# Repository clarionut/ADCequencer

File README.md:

# ADCequencer
An 8 step dual channel sequencer with voltage controlled step pattern, based on the [Fonitronik VCPS8](http://www.modular.fonik.de/pdf/VCPS8_doc_v2.pdf) (the predecessor of the MH11) but with significant modifications.

Most obviously, there are two potentiometers to set CV voltages for each step and two CV output channels. This gives considerable flexibility - e.g. controlling two VCOs, a VCO and filter cutoff, or (in conjunction with an external clock divider / analogue switch module) operation as a 16-step sequencer.

Another significant visible change is the addition of a 'freeze' circuit operated by switch or a gate input allowing the ADC to be stopped under voltage control. This gives real value to the gate output from the VCPS8 (which is on continously through a sequence of active steps) as it allows the sequencer pattern to be updated only when the trigger output is low (generally meaning that no note is sounding). This avoids a serious glitchy effect when a step is turned off while it's active.

Cosmetically, the LED arrays have been replaced by red/white common-cathode bicolour LEDs associated with each step (red shows the active steps and white the current step) plus a red/blue common-anode LED as an indicator for out-of-range pattern control voltages.

Behind the scenes there are also significant changes:
- the PCV out-of-range protection circuit in the original is essentially a zener diode crowbar across an op-amp output. This has been replaced by an in-line resistor and Schottky diodes to +5V and ground. The PCV out is not clipped by these, so it's easy to use an external voltmeter to check and adjust the incoming control voltage. The out-of-range LED circuitry is also modified so the LEDs are never reverse biased.
- the Gray-coding circuitry is included but can be bypassed by connecting to an alternative header on the PCB. The CD4030 XOR gates can be omitted altogether if Gray-coding is not required.
- the gate/trigger driver circuit has been significantly revised, doing away with the need for the CD40106 in the original (discussion at [Electro-Music.com](https://electro-music.com/forum/topic-52774-50.html)). A simple RC filter on the base of the trigger-driver transistor removes the very fast pulse from the AND gates which can cause double-triggering. The CD40106 is not needed for the ADC clock either, as the ADC802 contains an inverter gate and just needs an external resistor and capacitor to provide its own clock. The gate and trigger outputs are taken from a dedicated 9V supply rather than the raw 12V supply.

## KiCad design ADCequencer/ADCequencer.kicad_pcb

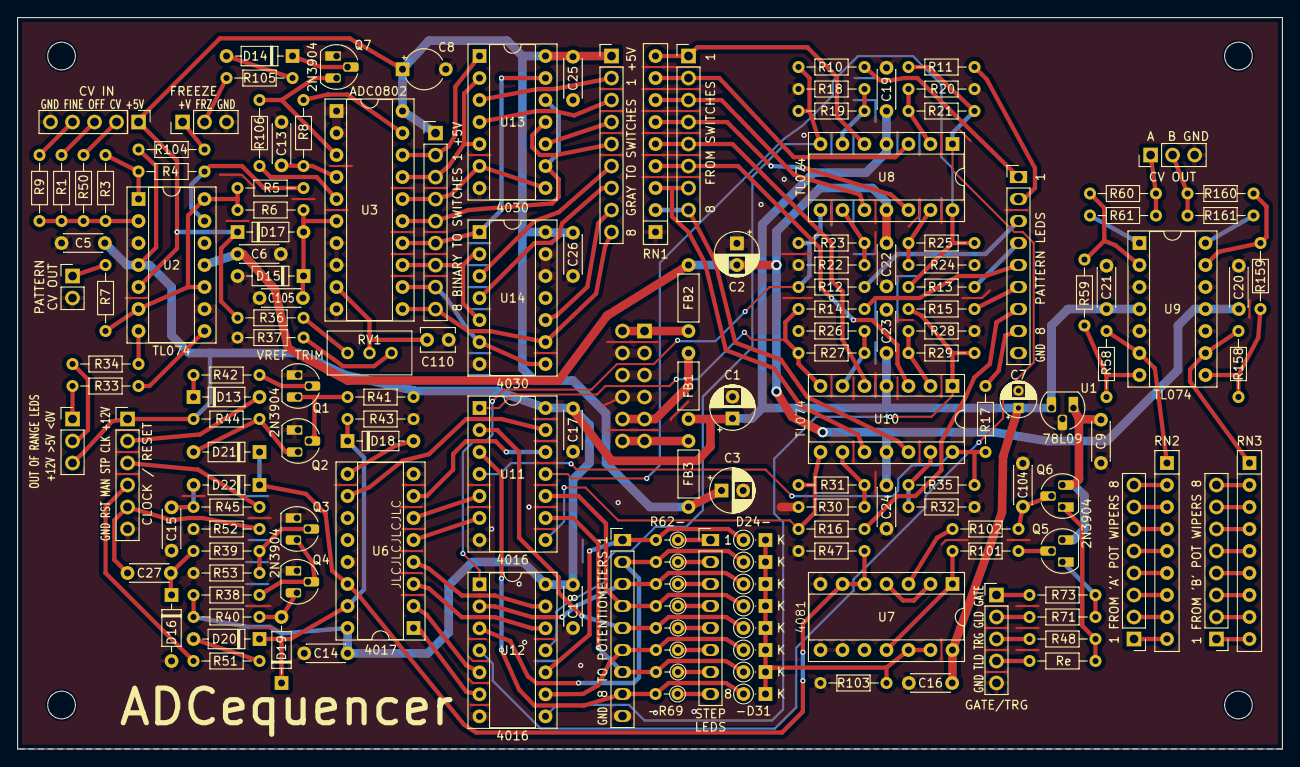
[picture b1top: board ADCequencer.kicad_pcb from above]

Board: 2 copper layers, 146.1 x 84.5 mm, 165 parts (1 on the bottom side), 158 nets.

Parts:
C1, C2, C3: 10u; CP_Radial_D5.0mm_P2.50mm
C5, C6, C9, C14, C15, C16, C17, C18, C19, C20, C21, C22, C23, C24, C25, C26, C105: 100n; C_Disc_D4.3mm_W1.9mm_P5.00mm
C7: 1u; CP_Radial_D4.0mm_P2.00mm
C8: 10u; CP_Radial_Tantal_D4.5mm_P5.00mm
C13: 150p; C_Disc_D4.3mm_W1.9mm_P5.00mm
C27: 10n; C_Disc_D4.3mm_W1.9mm_P5.00mm
C104: 1n; C_Disc_D4.3mm_W1.9mm_P5.00mm
C110: 100n; C_Disc_D3.8mm_W2.6mm_P2.50mm
D13, D14, D16, D18, D19, D20, D21, D22: 1N914; D_DO-35_SOD27_P7.62mm_Horizontal
D15, D17: BAT43; D_DO-35_SOD27_P7.62mm_Horizontal
D24, D25, D26, D27, D28, D29, D30, D31: 1N914; D_DO-35_SOD27_P2.54mm_Vertical_KathodeUp
FB1, FB2, FB3: FB; L_Axial_L5.3mm_D2.2mm_P7.62mm_Horizontal_Vishay_IM-1
J1: CLK/RST; PinHeader_1x06_P2.54mm_Vertical
J6: TO_POTS; PinHeader_1x09_P2.54mm_Vertical
J7: STEP_LEDS; PinHeader_1x08_P2.54mm_Vertical
J8: POWER; Power_2x06
J15: GATE/TRG; PinHeader_1x05_P2.54mm_Vertical
J16: WIPERS A; PinHeader_1x08_P2.54mm_Vertical
J17: WIPERS B; PinHeader_1x08_P2.54mm_Vertical
J18: CV OUT; PinHeader_1x03_P2.54mm_Vertical
J19: CV IN; PinHeader_1x05_P2.54mm_Vertical
J20: PCVOUT; PinHeader_1x02_P2.54mm_Vertical
J21: FREEZE; PinHeader_1x03_P2.54mm_Vertical
J25: OORLED; PinHeader_1x03_P2.54mm_Vertical
J26: BIN_TO_SW; PinHeader_1x09_P2.54mm_Vertical
J27: GRAY_TO_SW; PinHeader_1x09_P2.54mm_Vertical
J28: FROM_SW; PinHeader_1x08_P2.54mm_Vertical
J29: PLEDS; PinHeader_1x09_P2.54mm_Vertical
Q1, Q2, Q3, Q4, Q5, Q6, Q7: 2N3904; TO-92_HandSolder
R1, R3, R4, R5, R47, R50, R52, R53, R58, R59, R60, R103, R158, R159, R160: 100k; R_Axial_DIN0204_L3.6mm_D1.6mm_P7.62mm_Horizontal
R6, R8, R18, R20, R22, R24, R26, R28, R30, R32, R38, R40, R44, R45, R51, R101, R106: 10k; R_Axial_DIN0204_L3.6mm_D1.6mm_P7.62mm_Horizontal
R7, R48, R73: 1k; R_Axial_DIN0204_L3.6mm_D1.6mm_P7.62mm_Horizontal
R9: 2M2; R_Axial_DIN0204_L3.6mm_D1.6mm_P7.62mm_Horizontal
R10, R11, R12, R13, R14, R15, R16, R17: 6k8; R_Axial_DIN0204_L3.6mm_D1.6mm_P7.62mm_Horizontal
R19, R21, R23, R25, R27, R29, R31, R35: 20k; R_Axial_DIN0204_L3.6mm_D1.6mm_P7.62mm_Horizontal
R33, R71: 39k; R_Axial_DIN0204_L3.6mm_D1.6mm_P7.62mm_Horizontal
R34: 18k; R_Axial_DIN0204_L3.6mm_D1.6mm_P7.62mm_Horizontal
R36, R37: 51k; R_Axial_DIN0204_L3.6mm_D1.6mm_P7.62mm_Horizontal
R39, R41, R42, R43: 47k; R_Axial_DIN0204_L3.6mm_D1.6mm_P7.62mm_Horizontal
R61, R161: 470R; R_Axial_DIN0204_L3.6mm_D1.6mm_P7.62mm_Horizontal
R62, R63, R64, R65, R66, R67, R68, R69: 18k; R_Axial_DIN0204_L3.6mm_D1.6mm_P2.54mm_Vertical
R102: 22k; R_Axial_DIN0204_L3.6mm_D1.6mm_P7.62mm_Horizontal
R104: 12k; R_Axial_DIN0204_L3.6mm_D1.6mm_P7.62mm_Horizontal
R105: 27k; R_Axial_DIN0204_L3.6mm_D1.6mm_P7.62mm_Horizontal
REF1, REF2, REF3, REF4: Hole_3.2mm; MountingHole_3.2mm_M3
RN1, RN2, RN3: 100k; R_Array_SIP9
RV1: 50k; Potentiometer_Bourns_3296W_Vertical
Re: 39k; R_Axial_DIN0204_L3.6mm_D1.6mm_P7.62mm_Horizontal
U1: L78L09_TO92; TO-92_HandSolder
U2, U8, U9, U10: TL074; DIP-14_W7.62mm_Socket
U3: ADC0802; DIP-20_W7.62mm_Socket
U6: 4017; DIP-16_W7.62mm_Socket
U7: 4081; DIP-14_W7.62mm_Socket
U11, U12: 4016; DIP-14_W7.62mm_Socket
U13, U14: 4030; DIP-14_W7.62mm_Socket

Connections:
+5V: C3.1, C8.1, C25.1, C26.1, D17.1 (K), FB3.1, J19.1, J26.1, J27.1, R36.2, U2.5 (+), U3.20 (VCC), U13.14 (Vdd), U14.14 (Vdd)
+9V: C9.1, Q5.3 (C), Q6.3 (C), U1.1 (VO)
+12V: C1.1, C5.1, C7.1, C14.1, C16.1, C17.1, C18.1, C19.1, C21.1, C23.1, FB1.1, J1.1, J25.3, R38.2, R40.2, R41.2, R44.2, R104.2, U1.3 (VI), U2.4 (V+), U6.16 (VDD), U7.14 (VDD), U8.4 (V+), U9.4 (V+), U10.4 (V+), U11.14 (VDD), U12.14 (VDD)
-12V: C2.2, C6.1, C20.1, C22.1, C24.1, FB2.1, U2.11 (V-), U8.11 (V-), U9.11 (V-), U10.11 (V-)
/ADC board/<0V: J25.1, R33.2
/ADC board/>5V: J25.2, R34.2
/ADC board/B1: J26.2, U3.18 (DB0), U13.1
/ADC board/B2: J26.3, U3.17 (DB1), U13.2, U13.5
/ADC board/B3: J26.4, U3.16 (DB2), U13.6, U13.8
/ADC board/B4: J26.5, U3.15 (DB3), U13.9, U13.12
/ADC board/B5: J26.6, U3.14 (DB4), U13.13, U14.1
/ADC board/B6: J26.7, U3.13 (DB5), U14.2, U14.5
/ADC board/B7: J26.8, U3.12 (DB6), U14.6, U14.8
/ADC board/B8: J26.9, J27.9, U3.11 (DB7), U14.9
/ADC board/CV_IN: J19.2, R50.1
/ADC board/F+V: J21.1, R104.1
/ADC board/FINE: J19.4, R9.1
/ADC board/FRZ: J21.2, R105.1
/ADC board/G1: J27.2, U13.3
/ADC board/G2: J27.3, U13.4
/ADC board/G3: J27.4, U13.10
/ADC board/G4: J27.5, U13.11
/ADC board/G5: J27.6, U14.3
/ADC board/G6: J27.7, U14.4
/ADC board/G7: J27.8, U14.10
/ADC board/OFFSET: J19.3, R1.1
/ADC board/PCV: J20.1, R7.1
/ADC board/PLD1: J29.1, R10.2
/ADC board/PLD2: J29.2, R11.2
/ADC board/PLD3: J29.3, R12.2
/ADC board/PLD4: J29.4, R13.2
/ADC board/PLD5: J29.5, R14.2
/ADC board/PLD6: J29.6, R15.2
/ADC board/PLD7: J29.7, R16.2
/ADC board/PLD8: J29.8, R17.2
/ADC board/ST1: J28.1, RN1.9 (R8), U8.5 (+)
/ADC board/ST2: J28.2, RN1.8 (R7), U8.3 (+)
/ADC board/ST3: J28.3, RN1.7 (R6), U8.10 (+)
/ADC board/ST4: J28.4, RN1.6 (R5), U8.12 (+)
/ADC board/ST5: J28.5, RN1.5 (R4), U10.5 (+)
/ADC board/ST6: J28.6, RN1.4 (R3), U10.3 (+)
/ADC board/ST7: J28.7, RN1.3 (R2), U10.10 (+)
/ADC board/ST8: J28.8, RN1.2 (R1), U10.12 (+)
/CLK: D13.2 (A), J1.2
/GATE_LED: J15.2, R71.2
/GATE_OUT: J15.1, R73.2
/L1: J7.1, R62.1
/L2: J7.2, R63.1
/L3: J7.3, R64.1
/L4: J7.4, R65.1
/L5: J7.5, R66.1
/L6: J7.6, R67.1
/L7: J7.7, R68.1
/L8: J7.8, R69.1
/MAN_RST: J1.4, R51.1
/MAN_STP: J1.3, R45.1
/OUTA: J18.1, R60.2, R61.2
/OUTB: J18.2, R160.2, R161.2
/POT1: D24.2 (A), J6.1, R62.2, U12.10
/POT2: D25.2 (A), J6.2, R63.2, U12.3
/POT3: D26.2 (A), J6.3, R64.2, U12.2
/POT4: D27.2 (A), J6.4, R65.2, U11.10
/POT5: D28.2 (A), J6.5, R66.2, U11.2
/POT6: D29.2 (A), J6.6, R67.2, U12.9
/POT7: D30.2 (A), J6.7, R68.2, U11.9
/POT8: D31.2 (A), J6.8, R69.2, U11.3
/RESET: C27.1, J1.5, R52.2
/SS1: U6.3 (Q0), U12.12
/SS2: U6.2 (Q1), U12.5
/SS3: U6.4 (Q2), U12.13
/SS4: U6.7 (Q3), U11.12
/SS5: U6.10 (Q4), U11.13
/SS6: U6.1 (Q5), U12.6
/SS7: U6.5 (Q6), U11.6
/SS8: U6.6 (Q7), U11.5
/TRG_LED: J15.4, Re.2
/TRG_OUT: J15.3, R48.2
/W1A: J16.1, RN2.9 (R8)
/W1B: J17.1, RN3.9 (R8)
/W2A: J16.2, RN2.8 (R7)
/W2B: J17.2, RN3.8 (R7)
/W3A: J16.3, RN2.7 (R6)
/W3B: J17.3, RN3.7 (R6)
/W4A: J16.4, RN2.6 (R5)
/W4B: J17.4, RN3.6 (R5)
/W5A: J16.5, RN2.5 (R4)
/W5B: J17.5, RN3.5 (R4)
/W6A: J16.6, RN2.4 (R3)
/W6B: J17.6, RN3.4 (R3)
/W7A: J16.7, RN2.3 (R2)
/W7B: J17.7, RN3.3 (R2)
/W8A: J16.8, RN2.2 (R1)
/W8B: J17.8, RN3.2 (R1)
GND: C1.2, C2.1, C3.2, C5.2, C6.2, C7.2, C8.2, C9.2, C13.1, C14.2, C15.2, C16.2, C17.2, C18.2, C19.2, C20.2, C21.2, C22.2, C23.2, C24.2, C25.2, C26.2, C104.2, C105.1, C110.1, D15.2 (A), D16.2 (A), J1.6, J6.9, J8.3, J8.4, J8.5, J8.6, J8.7, J8.8, J15.5, J18.3, J19.5, J20.2, J21.3, J29.9, Q1.1 (E), Q2.1 (E), Q3.1 (E), Q4.1 (E), Q7.1 (E), R18.1, R20.1, R22.1, R24.1, R26.1, R28.1, R30.1, R32.1, R37.1, R43.1, R47.1, R52.1, R53.1, R103.1, RN1.1 (common), U1.2 (GND), U2.3 (+), U2.9 (-), U2.12 (+), U3.1 (CS), U3.2 (RD), U3.7 (VI-), U3.8 (AGND), U3.10 (DGND), U6.8 (VSS), U6.13 (CKEN), U7.7 (VSS), U7.8, U7.9, U9.3 (+), U9.5 (+), U9.10 (+), U9.12 (+), U11.7 (VSS), U12.7 (VSS), U13.7 (Vss), U14.7 (Vss), U14.12, U14.13
unnamed: D13.1 (K), R42.1
unnamed: D14.2 (A), R105.2
unnamed: D14.1 (K), Q7.2 (B)
unnamed: C105.2, D15.1 (K), D17.2 (A), R6.2, U3.6 (VI+)
unnamed: C27.2, D16.1 (K), R39.1
unnamed: D18.2 (A), U6.9 (Q8)
unnamed: D18.1 (K), D19.1 (K), D20.1 (K), R43.2, U6.15 (Reset)
unnamed: D19.2 (A), Q4.3 (C), R40.1
unnamed: D20.2 (A), R51.2
unnamed: D21.2 (A), Q2.3 (C), R44.1
unnamed: D21.1 (K), D22.1 (K), R47.2, U6.14 (CLK), U7.5, U7.6
unnamed: C15.1, D22.2 (A), R45.2
unnamed: D24.1 (K), D25.1 (K), D26.1 (K), D27.1 (K), D28.1 (K), D29.1 (K), D30.1 (K), D31.1 (K), R103.2, U7.12, U7.13
unnamed: FB2.2, J8.1, J8.2
unnamed: FB1.2, J8.9, J8.10
unnamed: FB3.2, J8.11, J8.12
unnamed: Q1.2 (B), R42.2
unnamed: Q1.3 (C), Q2.2 (B), R41.1
unnamed: Q3.2 (B), R39.2, R53.2
unnamed: Q3.3 (C), Q4.2 (B), R38.1
unnamed: Q5.2 (B), R101.2
unnamed: Q5.1 (E), R71.1, R73.1
unnamed: C104.1, Q6.2 (B), R102.2
unnamed: Q6.1 (E), R48.1, Re.1
unnamed: Q7.3 (C), R106.1, U3.3 (WR)
unnamed: R3.2, R4.1, U2.1
unnamed: R33.1, U2.8
unnamed: R34.1, U2.7
unnamed: R36.1, RV1.1
unnamed: R37.2, RV1.3
unnamed: R58.2, R59.1, U9.7
unnamed: R61.1, U9.1
unnamed: R101.1, U7.1, U7.11
unnamed: R102.1, U7.3
unnamed: R158.2, R159.1, U9.8
unnamed: R161.1, U9.14
unnamed: R58.1, RN2.1 (common), U9.6 (-)
unnamed: R158.1, RN3.1 (common), U9.9 (-)
unnamed: R1.2, R3.1, R9.2, R50.2, U2.2 (-)
unnamed: R5.2, R6.1, R7.2, U2.6 (-), U2.10 (+), U2.14
unnamed: R4.2, R5.1, U2.13 (-)
unnamed: C13.2, R8.2, U3.4 (CLK)
unnamed: R8.1, U3.19 (CLKR)
unnamed: R106.2, U3.5 (INTR)
unnamed: C110.2, RV1.2, U3.9 (VREF)
unnamed: U7.2, U7.4
unnamed: R20.2, R21.1, U8.2 (-)
unnamed: R18.2, R19.1, U8.6 (-)
unnamed: R22.2, R23.1, U8.9 (-)
unnamed: R24.2, R25.1, U8.13 (-)
unnamed: R59.2, R60.1, U9.2 (-)
unnamed: R159.2, R160.1, U9.13 (-)
unnamed: R28.2, R29.1, U10.2 (-)
unnamed: R26.2, R27.1, U10.6 (-)
unnamed: R30.2, R31.1, U10.9 (-)
unnamed: R32.2, R35.1, U10.13 (-)
STEP1: R10.1, R19.2, U8.7, U12.11
STEP2: R11.1, R21.2, U8.1, U12.4
STEP3: R12.1, R23.2, U8.8, U12.1
STEP4: R13.1, R25.2, U8.14, U11.11
STEP5: R14.1, R27.2, U10.7, U11.1
STEP6: R15.1, R29.2, U10.1, U12.8
STEP7: R16.1, R31.2, U10.8, U11.8
STEP8: R17.1, R35.2, U10.14, U11.4

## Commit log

2024-06-23 Create temp
